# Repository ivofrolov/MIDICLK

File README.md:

# MIDI Clock Converter

4HP eurorack module that provides two trigger outputs with an adjustable rhythm based on the incoming MIDI timing clock.

MIDI clock (24 PPQN) is read from TRS type A input. MIDI start message resets all clocks.

Adjust output clock rate using the clock divider encoder. Turn it clockwise to decrease the rate and counterclockwise to increase it. Press and hold while turning the knob to set the second clock divider.

Clock outputs provide about 3 milliseconds triggers.

# DIY

## Hardware

See [BOM](https://ivofrolov.github.io/MIDICLK/ibom.html) and board layout.

Schematic and PCB files are in the [hardware](/hardware) KiCad project folder, which also contains [panel design](/hardware/Panel.FCStd) FreeCad file.

## Firmware

Project is built using `make` in debug mode by default. In order to change mode use `make ENV=release build`. The same applies to other Makefile variables. Available targets are

  * `build` - compile firmware.elf file
  * `size` - display firmware size in bytes
  * `fuses` - program chip fuses bits
  * `upload` - write firmware to chip memory

In release mode reset is disabled (RSTDISBL fuse is programmed) due to lack of available pins.

# More ideas

  * [ ] offset control (half of the note duration)
  * [ ] triplet/dotted note switch
  * [ ] MIDI type A/B switch
  * [ ] gate length control (trigger or note duration)
  * [ ] customizable dividers

# References

  * [ATtiny USI UART](http://www.technoblogy.com/show?RPY=)
  * [Audio Jack Footprints](https://github.com/clacktronics/AudioJacks)

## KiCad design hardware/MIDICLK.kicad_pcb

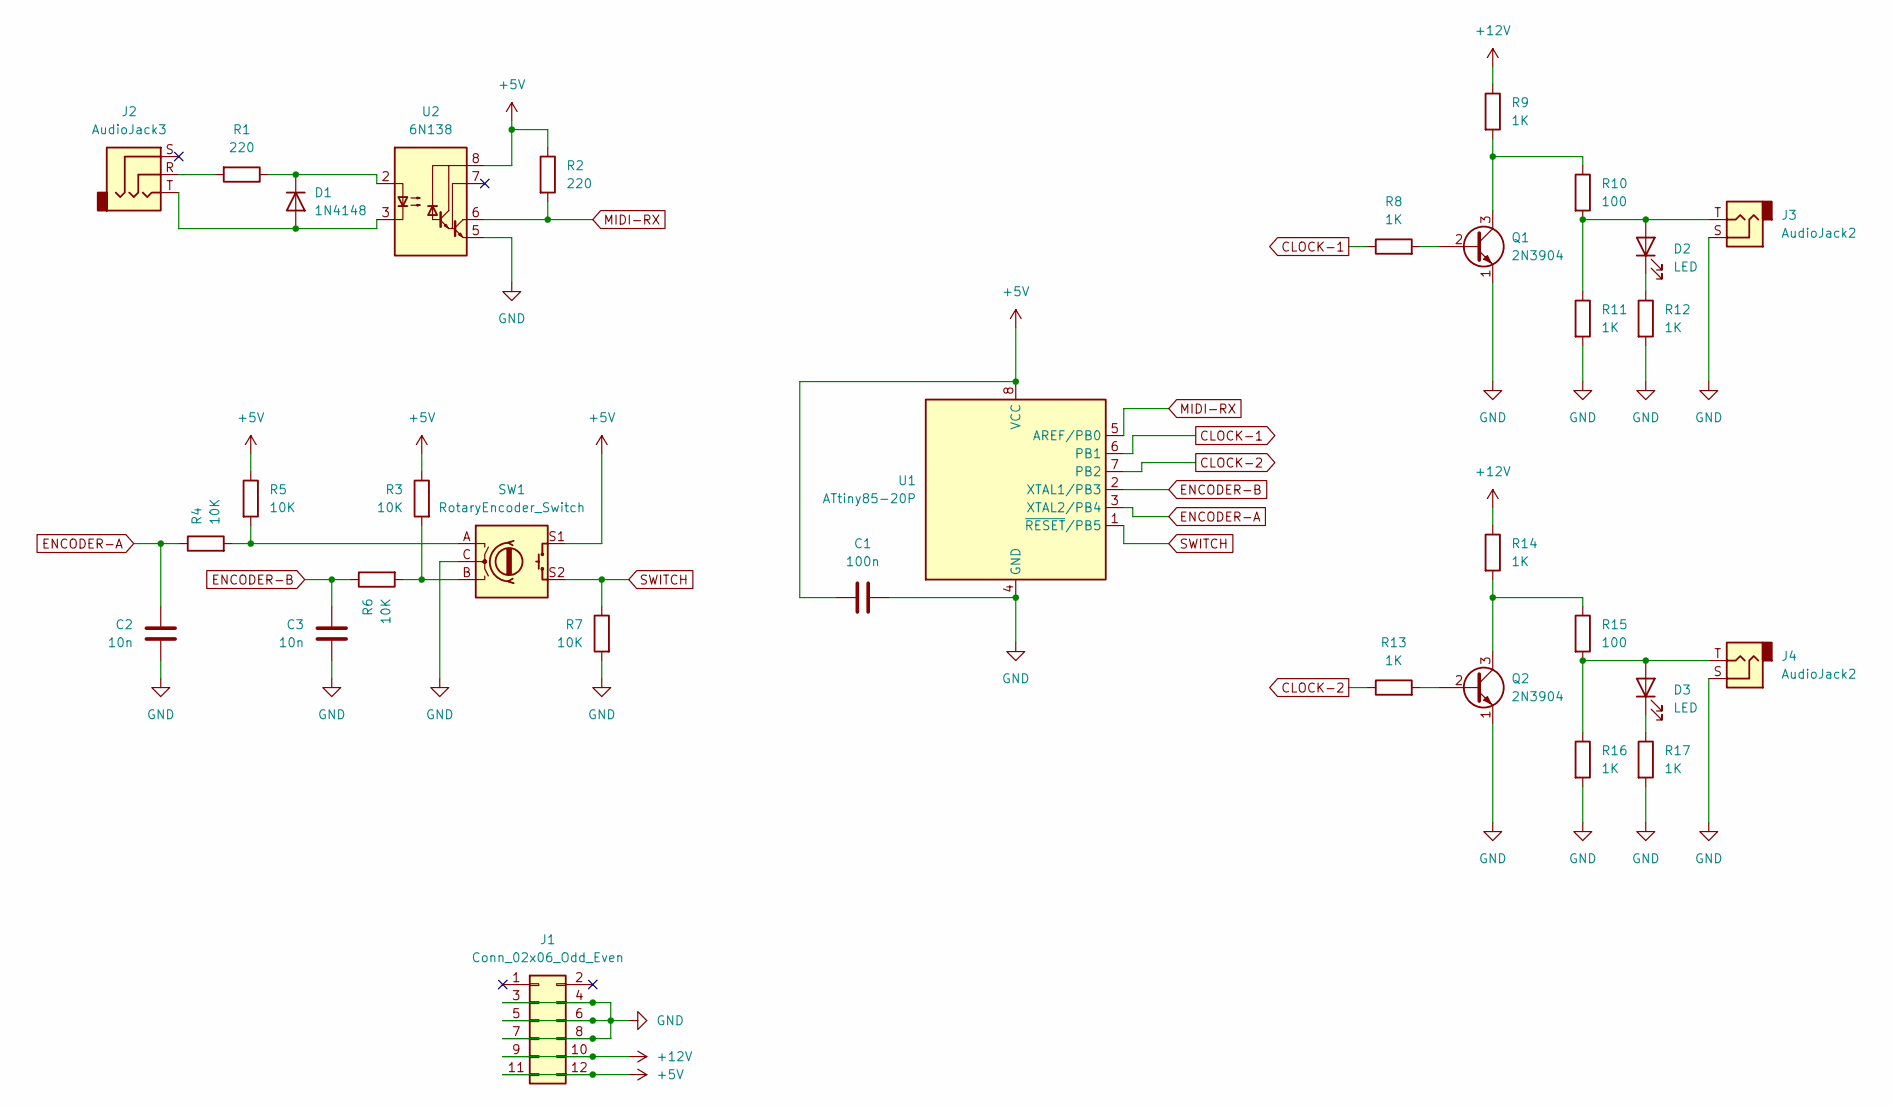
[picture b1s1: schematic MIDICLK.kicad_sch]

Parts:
C1: 100n; C_Disc_D5.0mm_W2.5mm_P5.00mm
C2, C3: 10n; C_Disc_D5.0mm_W2.5mm_P5.00mm
D1: 1N4148; D_DO-35_SOD27_P7.62mm_Horizontal
D2, D3: LED; LED_D3.0mm
J1: Conn_02x06_Odd_Even; IDC-Header_2x06_P2.54mm_Vertical
J2: AudioJack3; Jack_3.5mm_QingPu_WQP-PJ301CM_Vertical
J3, J4: AudioJack2; Jack_3.5mm_QingPu_WQP-PJ301M-12_Vertical
Q1, Q2: 2N3904; TO-92_Inline
R1, R2: 220; R_Axial_DIN0207_L6.3mm_D2.5mm_P2.54mm_Vertical
R3, R4, R5, R6, R7: 10K; R_Axial_DIN0207_L6.3mm_D2.5mm_P2.54mm_Vertical
R8, R9, R11, R12, R13, R14, R16, R17: 1K; R_Axial_DIN0207_L6.3mm_D2.5mm_P2.54mm_Vertical
R10, R15: 100; R_Axial_DIN0207_L6.3mm_D2.5mm_P2.54mm_Vertical
SW1: RotaryEncoder_Switch; RotaryEncoder_Alps_EC11E-Switch_Vertical_H20mm
U1: ATtiny85-20P; DIP-8_W7.62mm_Socket
U2: 6N138; DIP-8_W7.62mm_Socket

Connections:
+5V: C1.1, J1.11, J1.12, R2.1, R3.1, R5.1, SW1.S1, U1.8 (VCC), U2.8 (VCC)
+12V: J1.9, J1.10, R9.1, R14.1
CLOCK-1: R8.1, U1.6 (PB1)
CLOCK-2: R13.1, U1.7 (PB2)
ENCODER-A: C2.1, R4.1, U1.3 (XTAL2/PB4)
ENCODER-B: C3.1, R6.1, U1.2 (XTAL1/PB3)
GND: C1.2, C2.2, C3.2, J1.3, J1.4, J1.5, J1.6, J1.7, J1.8, J3.S, J4.S, Q1.1 (E), Q2.1 (E), R7.2, R11.2, R12.2, R16.2, R17.2, SW1.C, U1.4 (GND), U2.5 (GND)
MIDI-RX: R2.2, U1.5 (AREF/PB0), U2.6 (VO2)
unnamed: D1.2 (A), J2.T, U2.3 (C2)
unnamed: D1.1 (K), R1.1, U2.2 (C1)
unnamed: D2.2 (A), J3.T, R10.2, R11.1
unnamed: D2.1 (K), R12.1
unnamed: D3.2 (A), J4.T, R15.2, R16.1
unnamed: D3.1 (K), R17.1
unnamed: J2.R, R1.2
unnamed: Q1.2 (B), R8.2
unnamed: Q1.3 (C), R9.2, R10.1
unnamed: Q2.2 (B), R13.2
unnamed: Q2.3 (C), R14.2, R15.1
unnamed: R3.2, R6.2, SW1.B
unnamed: R4.2, R5.2, SW1.A
SWITCH: R7.1, SW1.S2, U1.1 (~RESET/PB5)

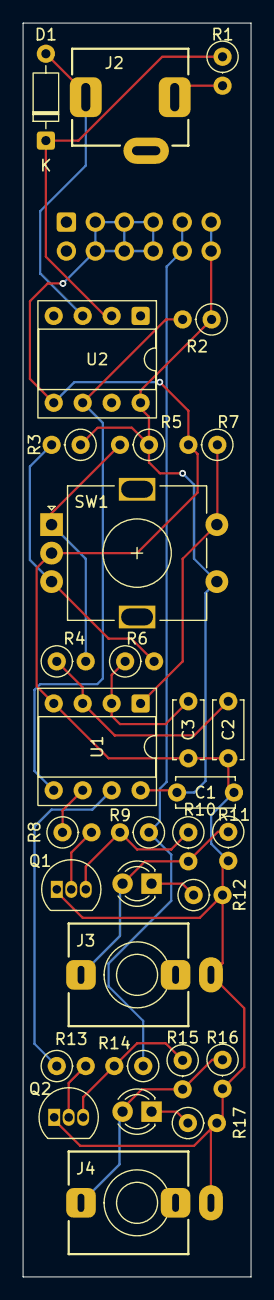
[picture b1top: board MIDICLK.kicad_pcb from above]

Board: 2 copper layers, 20.0 x 110.0 mm, 32 parts (1 on the bottom side), 22 nets.

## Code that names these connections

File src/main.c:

#include <avr/cpufunc.h>
#include <avr/interrupt.h>
#include <avr/io.h>
#include <util/delay.h>

/* IO

                 ATtiny85
                 ┌──◡──┐
   SWITCH    PB5 □1   8□ VCC
   ENCODER-B PB3 □2   7□ PB2 CLOCK-2
   ENCODER-A PB4 □3   6□ PB1 CLOCK-1
             GND □4   5□ PB0 MIDI-RX
                 └─────┘
 */
void setup_io() {
  DDRB = _BV(DDB2) | _BV(DDB1);      // pins 6 and 7 are outputs, others are inputs
  PORTB = _BV(PORTB2) | _BV(PORTB1); // set clock outputs high, pull-ups disabled
}

#define PPQN 24
// sent 24 timers per quarter note
#define MIDI_TIMING_CLOCK 0b11111000
#define MIDI_START 0b11111010

#define NOPTS 11
uint8_t CLKOPTS[NOPTS] = {
  1,        // original clock
  PPQN/8,   // 32nd
  PPQN/6,   // triplet 16th
  PPQN/4,   // 16th
  PPQN/3,   // triplet 8th
  PPQN/2,   // 8th
  PPQN*2/3, // triplet quarter
  PPQN,     // quarter
  PPQN*2,   // half
  PPQN*4,   // whole
  PPQN*8,   // double whole
};
uint8_t clksel1 = 3; // 16th
uint8_t clksel2 = 7; // quarter
uint8_t clkcnt1 = 0;
uint8_t clkcnt2 = 0;

uint8_t* cursel = &clksel1;

/* Set Timer1 to limit clock trigger time. */
void setup_clock_trigger_timer() {
  TCCR1 = _BV(CS13) | _BV(CS12) | _BV(CS11); // set prescaler to /8192 (~ 1 KHz)
  OCR1A = 2;                                 // set delay to ~ 3 ms
}

/* Turn off clock trigger. */
ISR (TIMER1_COMPA_vect) {
  PORTB |= _BV(PORTB2) | _BV(PORTB1); // set clocks high
  TIMSK &= ~_BV(OCIE1A);              // disable output compare match interrupt
}

/* Activate trigger and start timer to turn the signal off. */
void trigger_clocks() {
  if (clkcnt1 == 0 || clkcnt2 == 0) {
    TCNT1 = 0;            // reset counter
    TIFR |= _BV(OCF1A);   // clear output compare flag
    TIMSK |= _BV(OCIE1A); // enable output compare match interrupt
  }

  if (clkcnt1 == 0) {
    PORTB &= ~_BV(PORTB1); // set clock low
    clkcnt1 = CLKOPTS[clksel1];
  }
  --clkcnt1;

  if (clkcnt2 == 0) {
    PORTB &= ~_BV(PORTB2); // set clock low
    clkcnt2 = CLKOPTS[clksel2];
  }
  --clkcnt2;
}

void reset_clocks() {
  clkcnt1 = 0;
  clkcnt2 = 0;
}

void process_midi_message(uint8_t m) {
  switch (m) {
  case MIDI_START:
    reset_clocks();
    break;
  case MIDI_TIMING_CLOCK:
    trigger_clocks();
    break;
  }
}

void update_encoder_state() {
  static uint8_t last_value;
  // read encoder pins value (AB)
  uint8_t value = (PINB & (_BV(PINB4) | _BV(PINB3))) >> PINB3;
  if (value == last_value) {
    return;
  }
  last_value = value;

  static uint8_t last_enc;
  last_enc = (last_enc << 2) | value;
  if (last_enc == 0b01001011) { // one turn clockwise
    if (*cursel < NOPTS-1) {
      ++*cursel;
    }
  } else if (last_enc == 0b10000111) { // one turn counter clockwise
    if (*cursel > 0) {
      --*cursel;
    }
  }
}

void update_switch_state() {
  static uint8_t last_value;
  uint8_t value = bit_is_set(PINB, PINB5);
  if (value == last_value) {
    return;
  }

  // if (last_value != 0 && value == 0) {
  //   reset_clocks();
  // }

  last_value = value;

  if (value == 0) {
    cursel = &clksel1;
  } else {
    cursel = &clksel2;
  }
}

/* UART

   The ATtiny microcontroller does provide a hardware USI which can be used to
   implement half-duplex UART. The idea is as follows. The start of a byte causes a
   pin change interrupt (on falling edge). Then we want to get into the middle of a
   start bit (using a timer) to enable the USI to start shifting in the data bits. The
   clock source for the USI is a timer in CTC mode. The timer delay is derived from
   the CPU clock speed and baud rate in such a way that compare match occurs in the
   middle of the next bit. When 8 bits have been shifted in the USI overflow interrupt
   occurs so we can read the USI shift register and enable the pin change interrupt
   ready for the next byte.

   ──────┐  ┆  ┌──┆──┐  ┆     ┆  ┌──┆─────┆──┐  ┆  ┌──┆─────┆─────┆───
         └──┆──┘  ┆  └──┆─────┆──┘  ┆     ┆  └──┆──┘  ┆     ┆     ┆
   ┌─────┬─────┬─────┬─────┬─────┬─────┬─────┬─────┬─────┬─────┬─────┐
   │  1  │  0  │  1  │  0  │  0  │  1  │  1  │  0  │  1  │  1  │  1  │
   ├─────┼─────┼─────┼─────┼─────┼─────┼─────┼─────┼─────┼─────┼─────┤
   │idle │start│ D1  │ D2  │ D3  │ D4  │ D5  │ D6  │ D7  │ D8  │stop │
   └─────┴─────┴─────┴─────┴─────┴─────┴─────┴─────┴─────┴─────┴─────┘

   See http://www.technoblogy.com/show?RPY=

   MIDI messages are made up of 8-bit bytes transmitted at 31 250 baud using 8-N-1
   asynchronous serial communication (8 data bits, no parity, 1 stop bit). So in our
   case of 8 MHz clock the duration of one bit is 8000000/31250=256 clock cycles. */
void setup_uart() {
  USICR = 0;            // disable USI
  GIFR = _BV(PCIF);     // clear pin change interrupt flag
  GIMSK |= _BV(PCIE);   // enable pin change interrupts
  PCMSK |= _BV(PCINT0); // enable pin 5 change interrupt
}

/* Wait for a start bit (falling edge) and setup timer to one-half of the bit time. */
ISR (PCINT0_vect) {
  if (!(PINB & _BV(PINB0))) {
    GIMSK &= ~_BV(PCIE);      // disabe pin change interrupts
    TCCR0A = _BV(WGM01);      // set clear timer on compare match (CTC) mode
    TCCR0B = _BV(CS01);       // set prescaler to /8
    TCNT0 = 0;                // reset counter
    OCR0A = 15;               // set delay to (15+1)*8=128 cycles
    TIFR |= _BV(OCF0A);       // clear output compare flag
    TIMSK |= _BV(OCIE0A);     // enable output compare match interrupt
  }
}

/* When start bit is detected setup timer to the one bit time and start receiving. */
ISR (TIMER0_COMPA_vect) {
  TIMSK &= ~_BV(OCIE0A);             // disable output compare match interrupt
  TCNT0 = 0;                         // reset counter
  OCR0A = 31;                        // set delay to (31+1)*8=256 cycles
  USICR = _BV(USIOIE) | _BV(USICS0); // enable USI overflow interrupt and select timer
                                     // compare match as a clock source
  USISR = _BV(USIOIF) | 8;           // clear USI overflow interrupt flag and set
                                     // counter to read one byte
}

uint8_t reverse_byte(uint8_t x) {
  x = ((x >> 1) & 0x55) | ((x << 1) & 0xAA);
  x = ((x >> 2) & 0x33) | ((x << 2) & 0xCC);
  x = ((x >> 4) & 0x0F) | ((x << 4) & 0xF0);
  return x;
}

/* Read byte after 8 bits have been shifted and start waiting for the next. */
ISR (USI_OVF_vect) {
  USICR = 0;                           // disable USI
  uint8_t value = reverse_byte(USIBR); // read value from the buffer (USI assumes MSB
                                       // first but UART sends bits LSB first)

  process_midi_message(value);

  GIFR = _BV(PCIF);   // clear pin change interrupt flag
  GIMSK |= _BV(PCIE); // enable pin change interrupts again
}

/* MAIN LOOP */
int main() {
  cli();
  setup_io();
  setup_clock_trigger_timer();
  reset_clocks();
  setup_uart();
  sei();

  for (;;) {
    update_switch_state();
    update_encoder_state();
    _delay_ms(1);
  }
}

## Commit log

2025-09-02 Initial commit (work in progress)
2025-09-07 Quick fix protoboard layout
2025-09-09 Invert output pins signal
2025-09-09 Assign footprints to components
2025-09-11 Make PCB
2025-10-13 Add panel
2025-10-14 Add description
2025-10-14 Exclude pages folder from diff and repo statistics
2025-10-14 Configure pages folder
2025-10-14 Fix ibom url
2025-10-15 Fix avrdude commandline
2026-06-14 Switch to Makefile build
